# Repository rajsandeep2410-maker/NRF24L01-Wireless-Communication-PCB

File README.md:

# 🚀 NRF24L01 Wireless Communication PCB

## 📌 Overview
This project demonstrates a wireless communication system using NRF24L01 modules and Arduino, designed with a custom PCB in KiCad.

The design includes both:
- Transmitter (TX) section
- Receiver (RX) section

placed on a single board for demonstration and learning purposes.

---

## 🔧 Features
- NRF24L01-based wireless communication  
- Arduino interface for control and processing  
- Custom PCB design using KiCad  
- Power regulation and decoupling components  
- Clearly separated TX and RX sections  

---

## ⚙️ Working Principle
- The transmitter sends data wirelessly using the NRF24L01 module  
- The receiver captures the signal and processes it using Arduino  
- The received signal can be used to control outputs like LEDs or motors  

---

## ⚠️ Important Note
The transmitter and receiver are implemented as independent systems on the same PCB for demonstration purposes.

- Blue airwires (ratsnest) represent logical connections from the schematic  
- These are intentionally left unrouted to maintain separation between TX and RX sections  

---

## 🛠️ Tools Used
- KiCad (PCB Design)  
- Arduino IDE  

---

## 📂 Project Files
- Schematic (.kicad_sch)  
- PCB Layout (.kicad_pcb)  
- Project File (.kicad_pro)  

---

## 🚀 Future Improvements
- Fabricate and test the PCB  
- Add real-time demo (LED/motor control)  
- Optimize layout for compact design  

---

## 📸 Demo (Coming Soon)
A working demonstration video will be added soon showing wireless communication between transmitter and receiver.

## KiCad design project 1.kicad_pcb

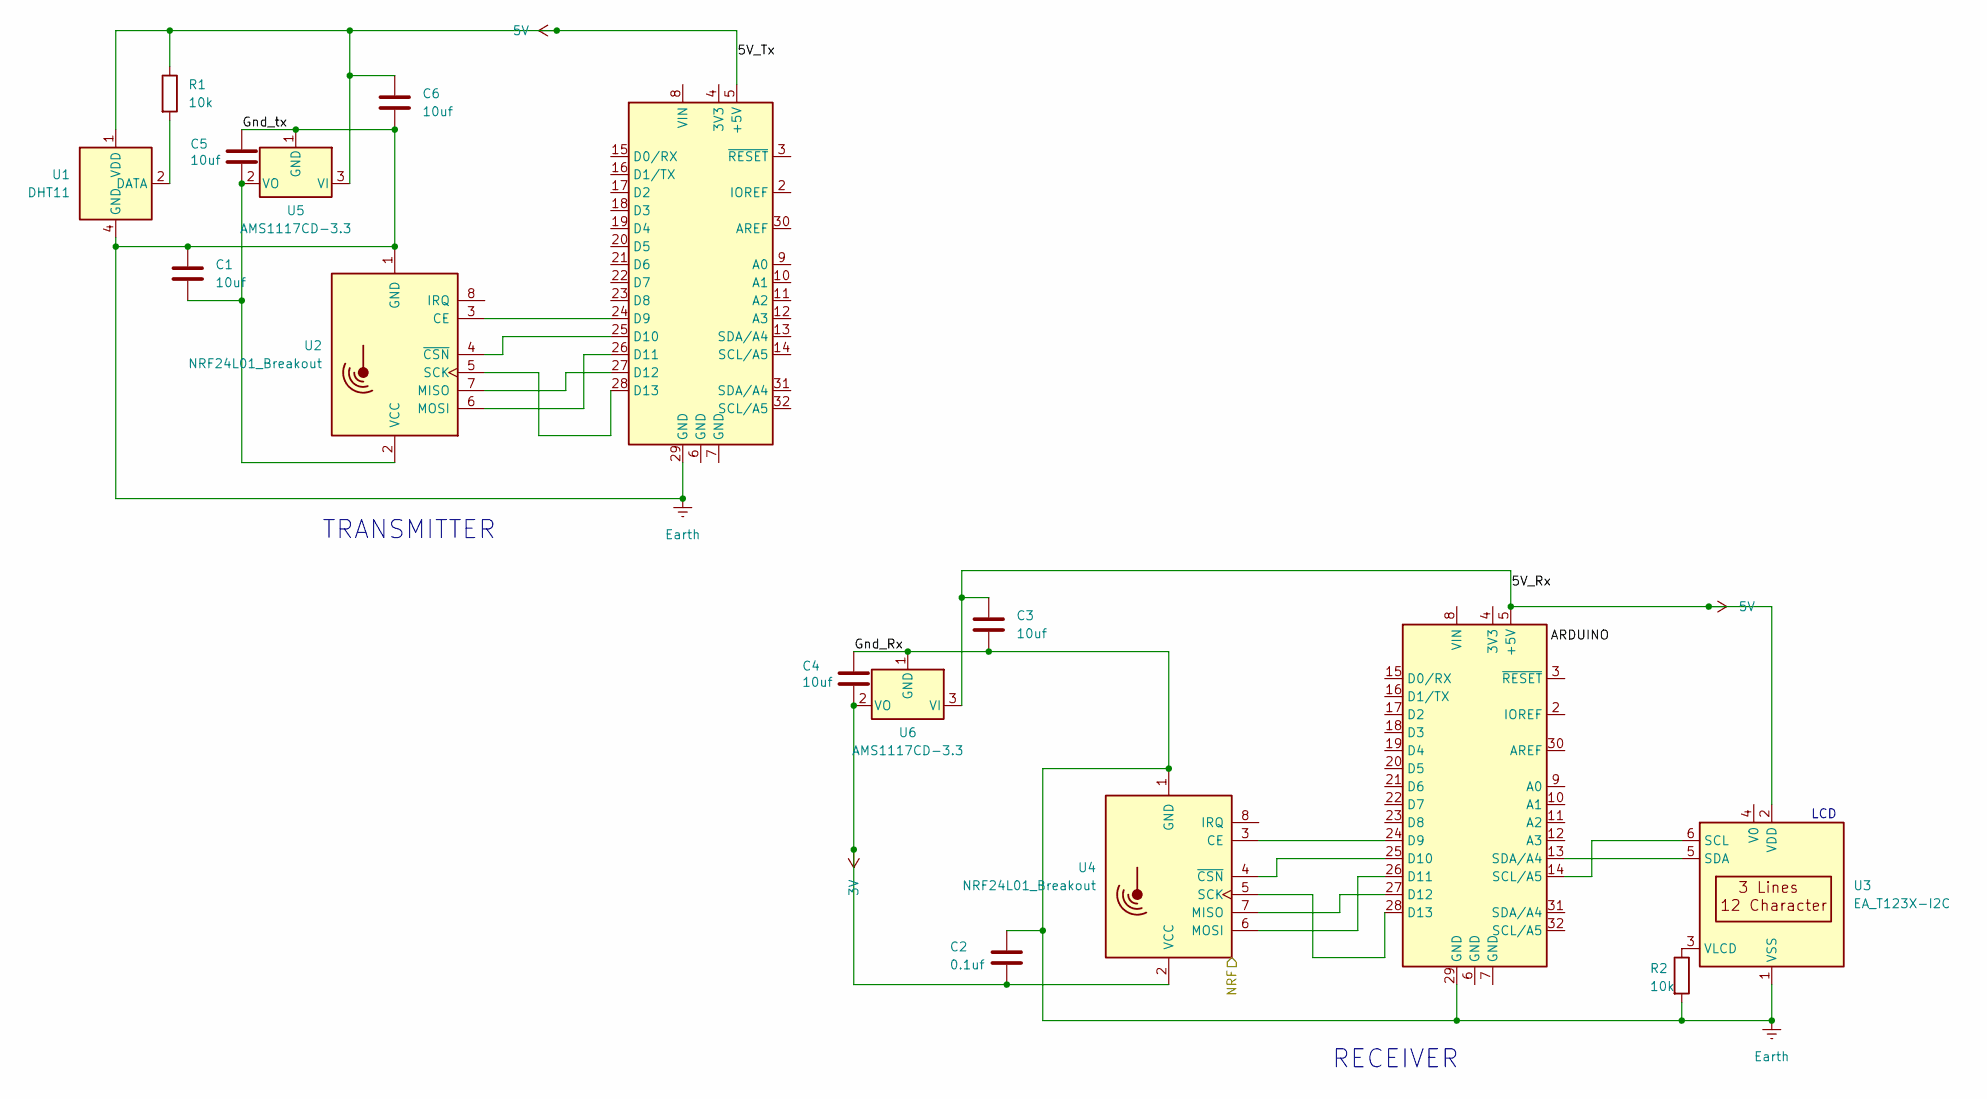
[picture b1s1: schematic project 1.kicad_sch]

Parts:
A1, A2: Arduino_UNO_R3
C1, C3, C4, C5, C6: 10uf; SOT-223-3_TabPin2
C2: 0.1uf; C_0805_2012Metric
R1, R2: 10k; R_0805_2012Metric
U1: DHT11; FanPinHeader_1x04_P2.54mm_Vertical
U2, U4: NRF24L01_Breakout; PinHeader_1x08_P2.54mm_Horizontal
U3: EA_T123X-I2C; PinHeader_1x06_P2.54mm_Horizontal
U5, U6: AMS1117CD-3.3; SOT-223-3_TabPin2

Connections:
3V: C2.2, C4.2, U4.2 (VCC), U6.2 (VO)
5V: A1.5 (+5V), A2.5 (+5V), C3.1, C6.1, R1.1, U1.1 (VDD), U3.2 (VDD), U5.3 (VI), U6.3 (VI)
Earth: A1.29 (GND), A2.29 (GND), C1.1, C2.1, C3.2, C4.1, C5.1, C6.2, R2.2, U1.4 (GND), U2.1 (GND), U3.1 (VSS), U4.1 (GND), U5.1 (GND), U6.1 (GND)
unnamed: A1.24 (D9), U2.3 (CE)
unnamed: A1.25 (D10), U2.4 (~CSN)
unnamed: A1.26 (D11), U2.6 (MOSI)
unnamed: A1.27 (D12), U2.7 (MISO)
unnamed: A1.28 (D13), U2.5 (SCK)
unnamed: A2.24 (D9), U4.3 (CE)
unnamed: A2.25 (D10), U4.4 (~CSN)
unnamed: A2.26 (D11), U4.6 (MOSI)
unnamed: A2.27 (D12), U4.7 (MISO)
unnamed: A2.28 (D13), U4.5 (SCK)
unnamed: R1.2, U1.2 (DATA)
unnamed: C1.2, C5.2, U2.2 (VCC), U5.2 (VO)
unnamed: A2.14 (SCL/A5), U3.6 (SCL)
unnamed: A2.13 (SDA/A4), U3.5 (SDA)
unnamed: R2.1, U3.3 (VLCD)

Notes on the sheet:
LCD
TRANSMITTER
RECEIVER

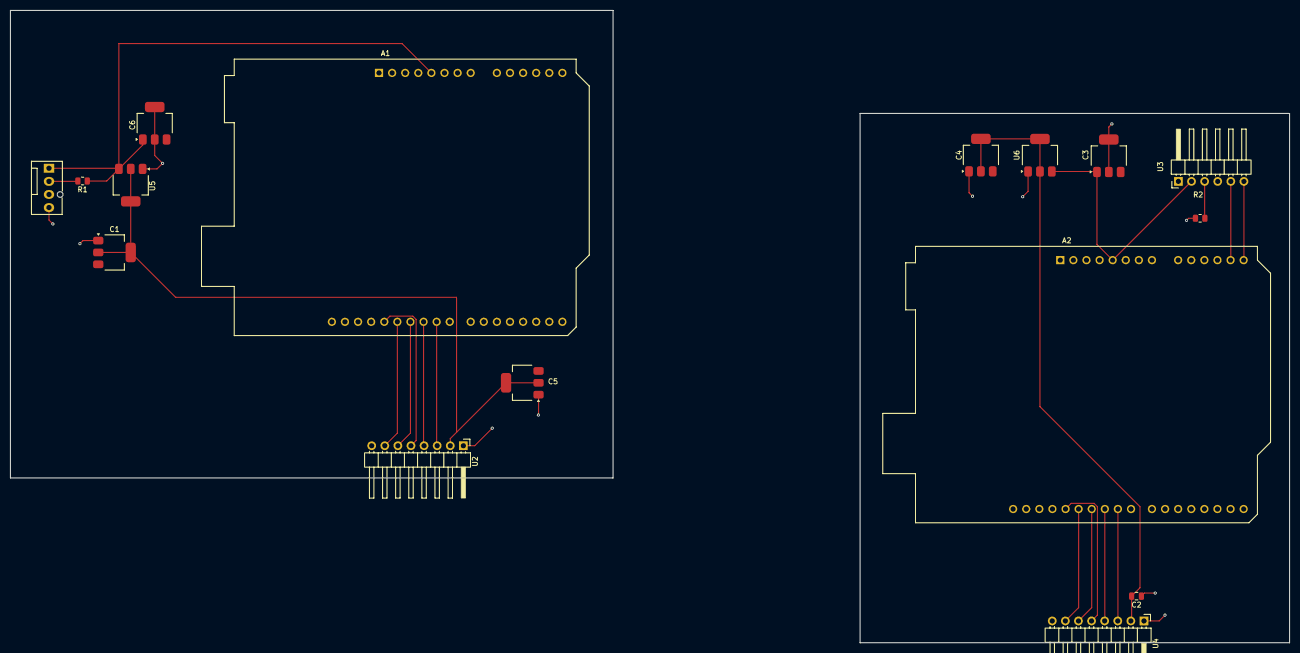
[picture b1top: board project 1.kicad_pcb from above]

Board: 2 copper layers, 248.0 x 122.6 mm, 16 parts (0 on the bottom side), 18 nets.

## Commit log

2026-04-17 Revise README for NRF24L01 Wireless Communication PCB
    Updated README to enhance project overview and features.
